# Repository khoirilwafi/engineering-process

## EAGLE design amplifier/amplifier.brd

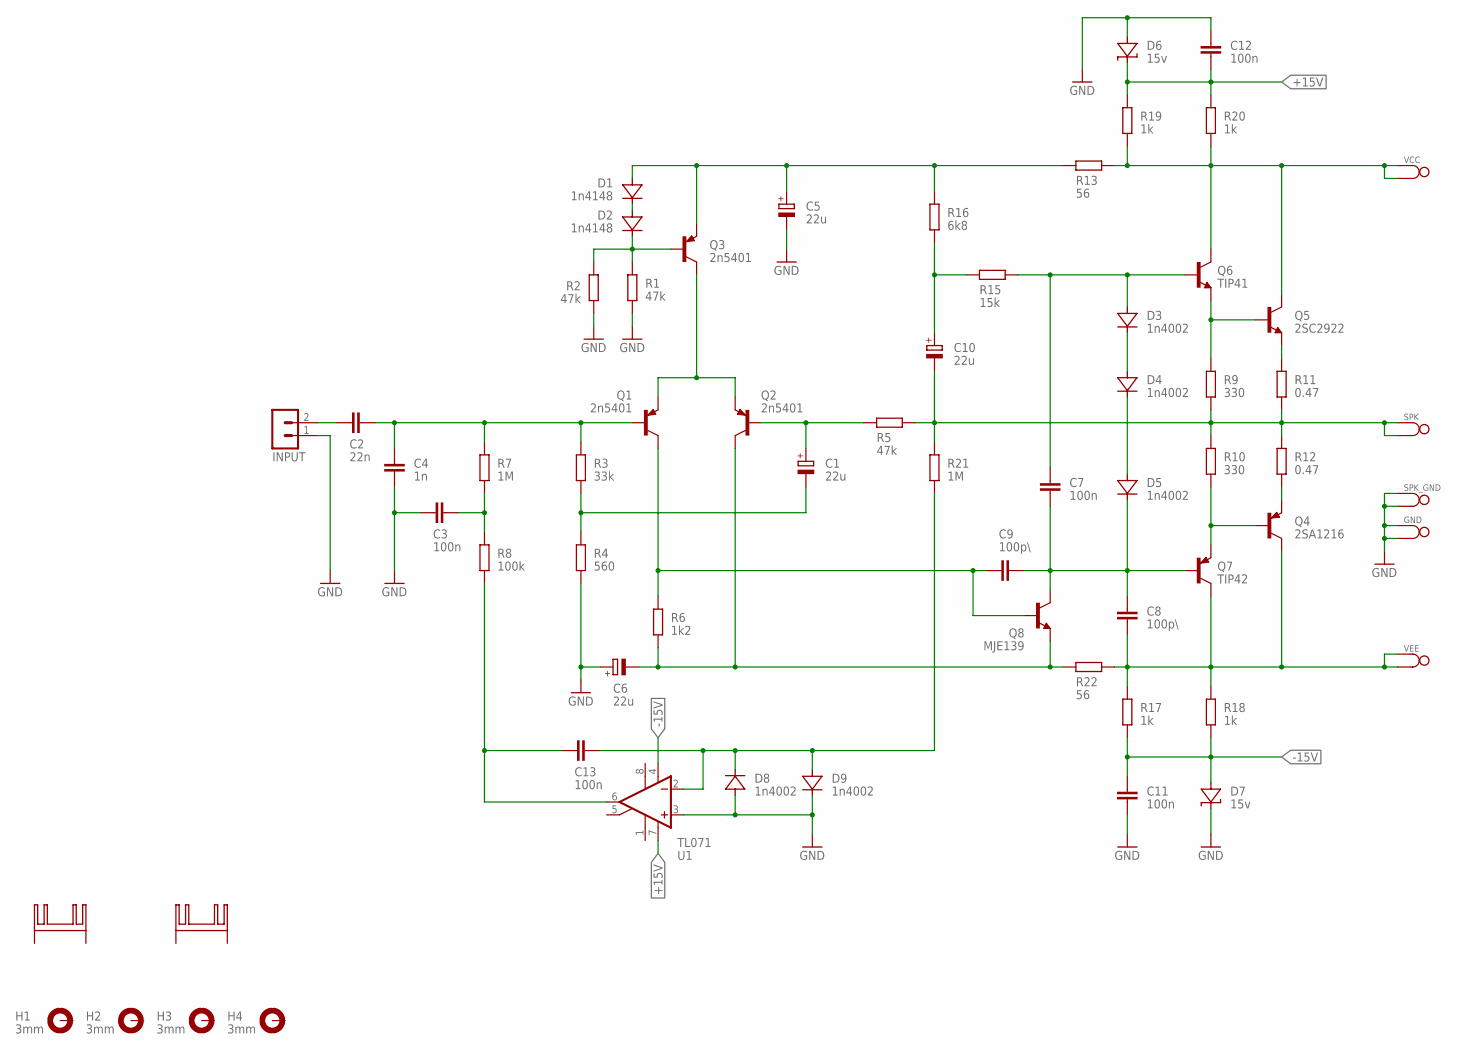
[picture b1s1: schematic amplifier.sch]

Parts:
C1: 22u; E2,5-6
C2: 22n; C050-024X044
C3, C7, C11, C12, C13: 100n; C050-024X044
C4: 1n; C050-024X044
C5, C6, C10: 22u; E3,5-8
C8, C9: 100p\; C050-024X044
CON1: INPUT; 2P
D1, D2: 1n4148; DO35Z7
D3, D4, D5, D8, D9: 1n4002; DO35Z7
D6, D7: 15v; DO35Z7
GND: SPADE; SPADE-POWER
H1, H2, H3, H4: 3mm; 3,0-PAD
KK1, KK2: SK104-PAD
Q1, Q2, Q3: 2n5401; TO92-BCE
Q4: 2SA1216; MT200L
Q5: 2SC2922; MT200L
Q6: TIP41; TO220V
Q7: TIP42; TO220V
Q8: MJE139; TO126V
R1, R2, R5: 47k; 0309/12
R3: 33k; 0309/12
R4: 560; 0309/12
R6: 1k2; 0309/12
R7, R21: 1M; 0309/12
R8: 100k; 0309/12
R9, R10: 330; 0617/17
R11, R12: 0.47; 0922/22
R13, R22: 56; 0309/12
R15: 15k; 0309/12
R16: 6k8; 0309/12
R17, R18, R19, R20: 1k; 0309/12
SPK: SPADE; SPADE-POWER
SPK_GND: SPADE; SPADE-POWER
U1: TL071; DIL08
VCC: SPADE; SPADE-POWER
VEE: SPADE; SPADE-POWER

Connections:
+15V: C12.1, D6.C, R19.2, R20.2, U1.7 (V+)
-15V: C11.2, D7.A, R17.1, R18.1, U1.4 (V-)
GND: C3.1, C4.1, C5.-, C6.+, C11.1, C12.2, CON1.1, D6.A, D7.C, D8.A, D9.C, GND.P$1, GND.P$2, R1.1, R2.1, R4.1, SPK_GND.P$1, SPK_GND.P$2, U1.3 (+IN)
unnamed: D2.C, Q3.B, R1.2, R2.2
unnamed: D1.C, D2.A
unnamed: Q5.C, Q6.C, R13.1, R19.1, R20.1, VCC.P$1, VCC.P$2
unnamed: C2.2, C4.2, Q1.B, R3.2, R7.2
unnamed: C1.-, R3.1, R4.2
unnamed: C1.+, Q2.B, R5.2
unnamed: C13.2, D8.C, D9.A, R21.1, U1.2 (-IN)
unnamed: Q1.E, Q2.E, Q3.C
unnamed: C3.2, R7.1, R8.2
unnamed: Q4.E, R12.1
unnamed: C2.1, CON1.2
unnamed: C10.-, R5.1, R9.1, R10.2, R11.1, R12.2, R21.2, SPK.P$1, SPK.P$2
unnamed: Q5.E, R11.2
unnamed: C7.2, D3.A, Q6.B, R15.1
unnamed: Q4.B, Q7.E, R10.1
unnamed: Q5.B, Q6.E, R9.2
unnamed: D3.C, D4.A
unnamed: D4.C, D5.A
unnamed: C7.1, C8.1, C9.2, D5.C, Q7.B, Q8.C
unnamed: C9.1, Q1.C, Q8.B, R6.2
unnamed: C8.2, Q4.C, Q7.C, R17.2, R18.2, R22.1, VEE.P$1, VEE.P$2
unnamed: C6.-, Q2.C, Q8.E, R6.1, R22.2
unnamed: C5.+, D1.A, Q3.E, R13.2, R16.2
unnamed: C10.+, R15.2, R16.1
unnamed: C13.1, R8.1, U1.6 (OUT)

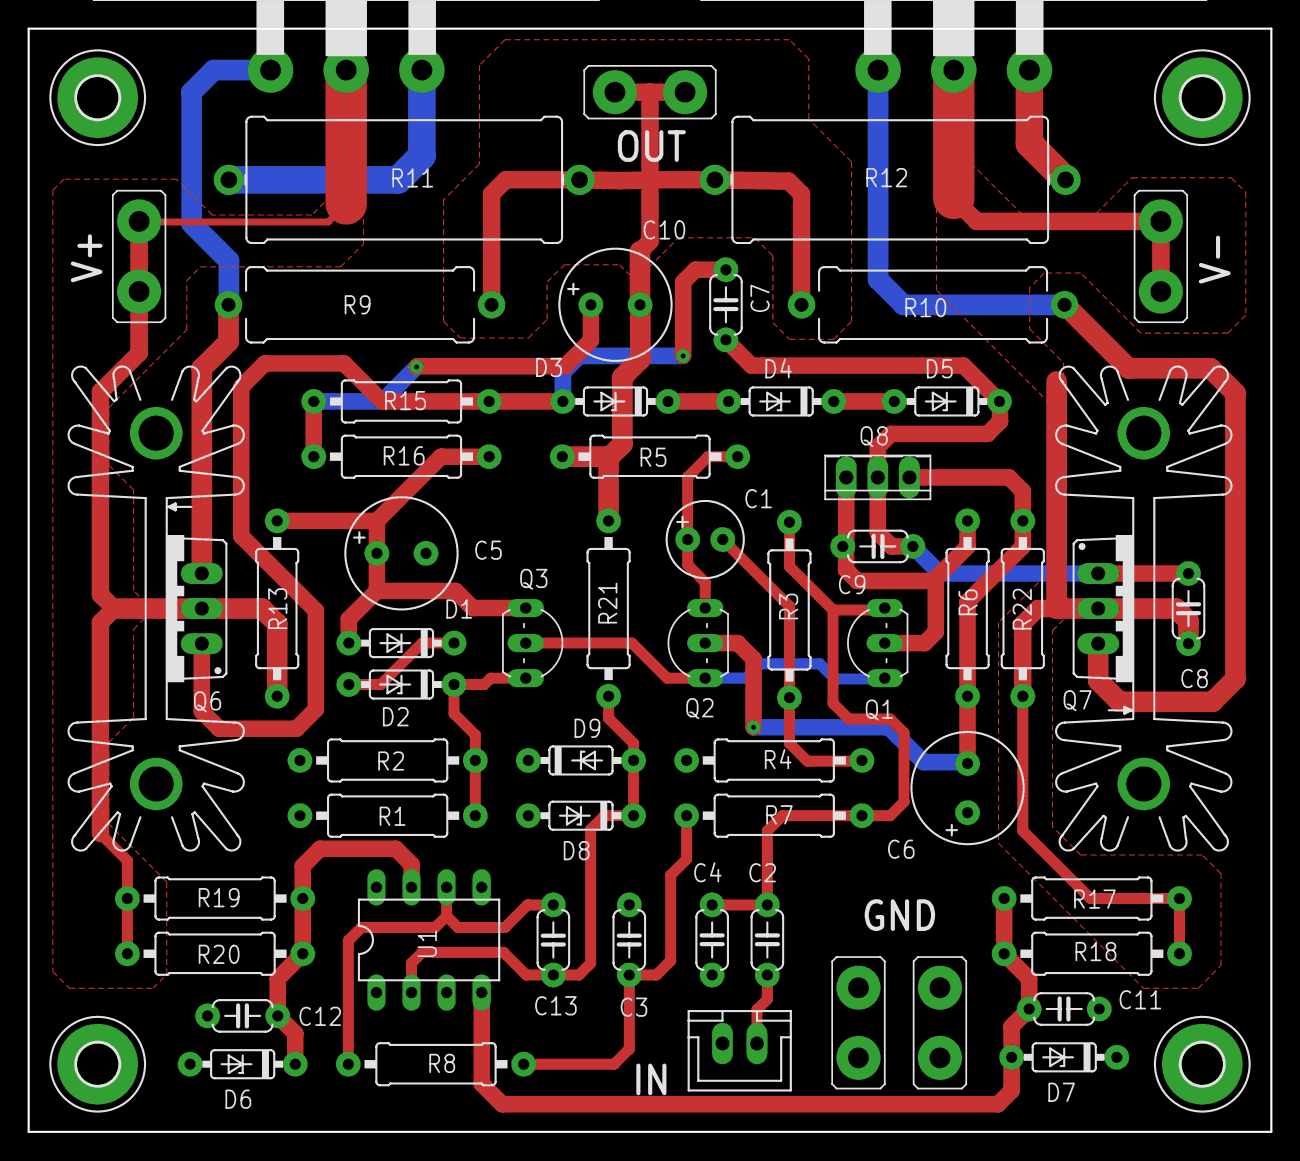
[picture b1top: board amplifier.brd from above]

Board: 2 copper layers, 90.0 x 79.9 mm, 64 parts (0 on the bottom side), 28 nets.
